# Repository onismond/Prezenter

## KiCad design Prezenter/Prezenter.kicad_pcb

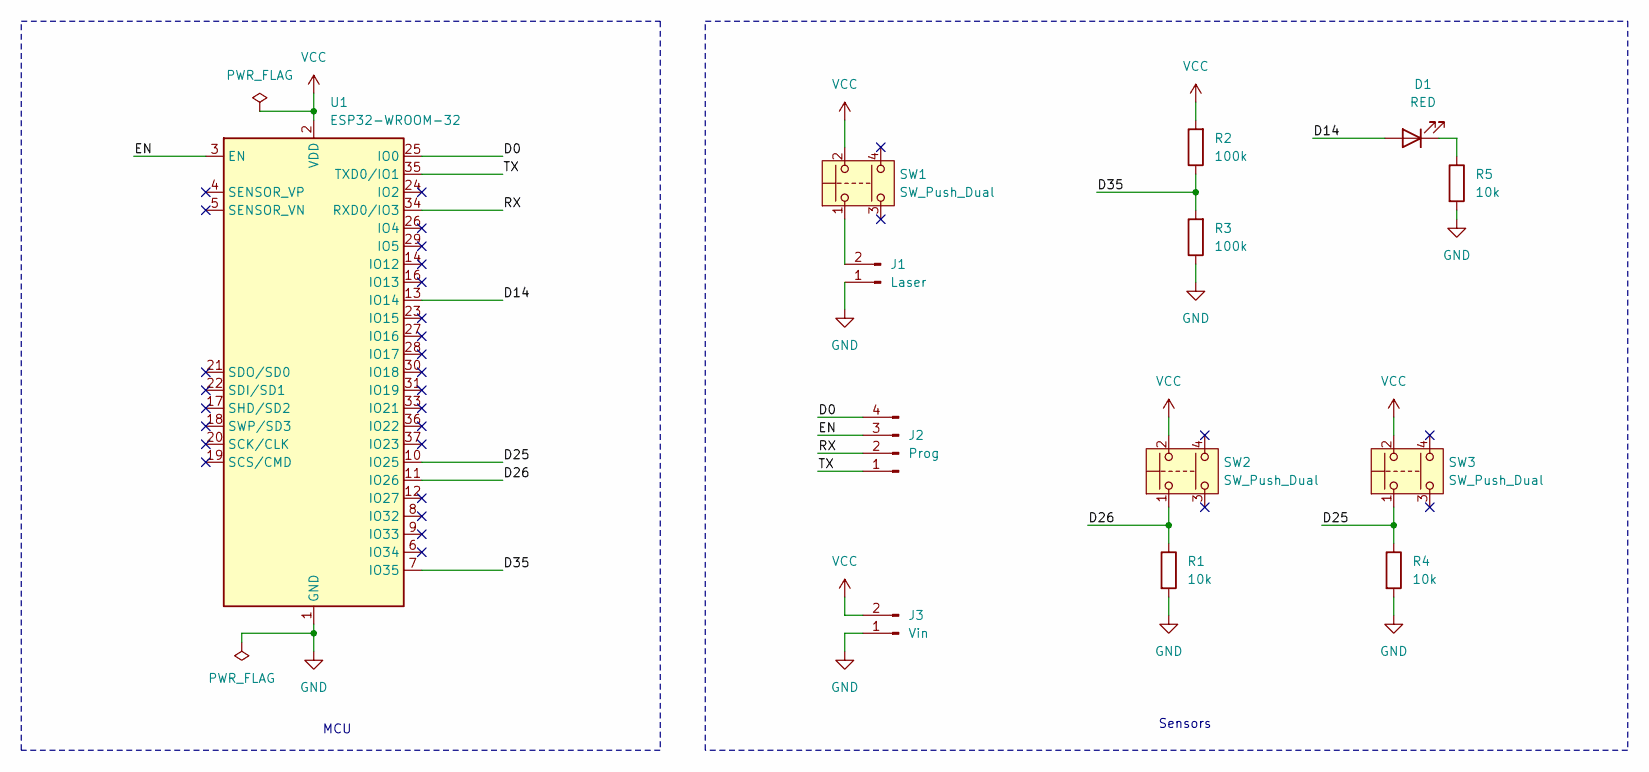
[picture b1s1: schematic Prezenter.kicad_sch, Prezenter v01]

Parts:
D1: RED; LED_D5.0mm
J1: Laser; PinHeader_1x02_P2.54mm_Vertical
J2: Prog; PinHeader_1x04_P2.54mm_Vertical
J3: Vin; PinHeader_1x02_P2.54mm_Vertical
R1, R4, R5: 10k; R_Axial_DIN0207_L6.3mm_D2.5mm_P10.16mm_Horizontal
R2, R3: 100k; R_Axial_DIN0207_L6.3mm_D2.5mm_P10.16mm_Horizontal
SW1, SW2, SW3: SW_Push_Dual; SW_PUSH_12mm
U1: ESP32-WROOM-32

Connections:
/D0: J2.4, U1.25 (IO0)
/D14: D1.2 (A), U1.13 (IO14)
/D25: R4.1, SW3.1, U1.10 (IO25)
/D26: R1.1, SW2.1, U1.11 (IO26)
/D35: R2.1, R3.2, U1.7 (IO35)
/EN: J2.3, U1.3 (EN)
/RX: J2.2, U1.34 (RXD0/IO3)
/TX: J2.1, U1.35 (TXD0/IO1)
GND: J1.1, J3.1, R1.2, R3.1, R4.2, R5.2, U1.1 (GND), U1.15 (GND), U1.38 (GND), U1.39 (GND)
unnamed: D1.1 (K), R5.1
unnamed: J1.2, SW1.1
VCC: J3.2, R2.2, SW1.2, SW2.2, SW3.2, U1.2 (VDD)

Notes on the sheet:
Sensors
MCU

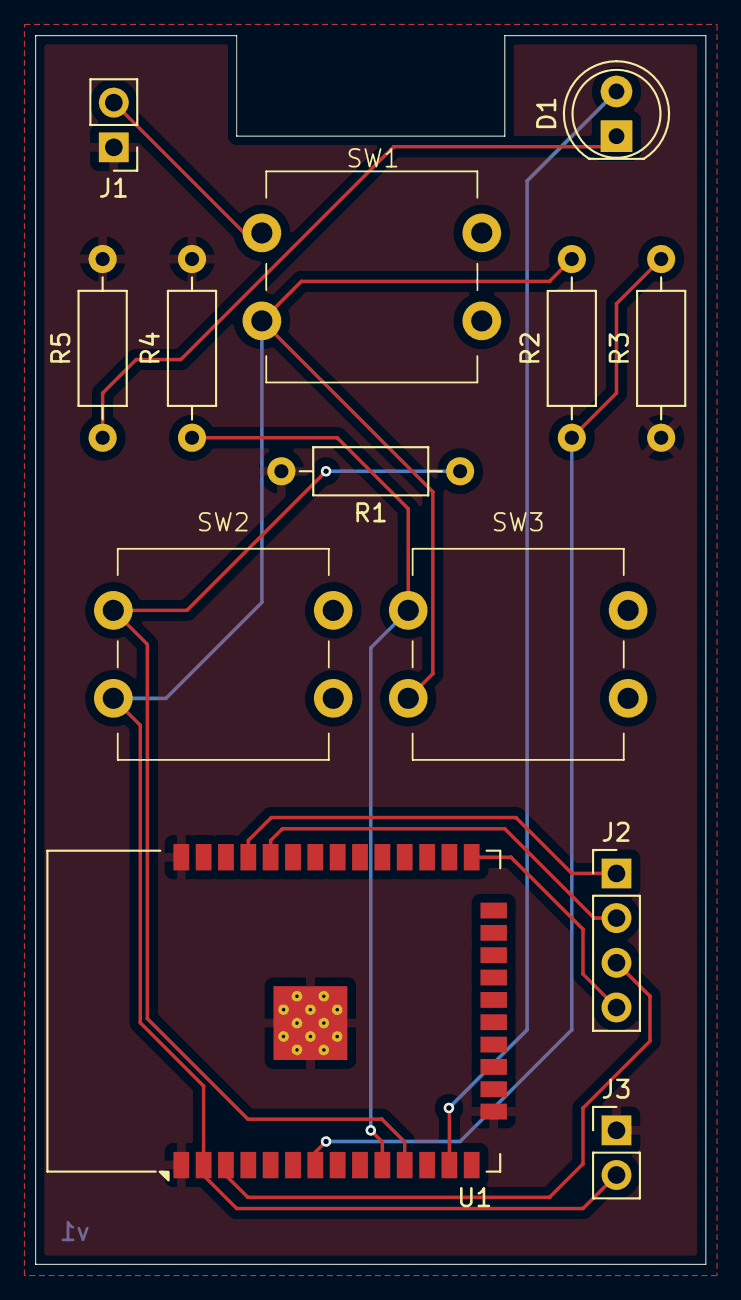
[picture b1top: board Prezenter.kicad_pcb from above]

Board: 2 copper layers, 38.1 x 69.8 mm, 13 parts (0 on the bottom side), 12 nets.
